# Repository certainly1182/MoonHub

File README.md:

# MoonHub - Unified Daughterboard-esque USB 2.0 Hub
This repository contains the hardware for a USB hub designed for mechanical keyboards.
Designed for use with the [MoonBoard](https://github.com/certainly1182/MoonBoard).

## Features
- USB-C input, 1x USB-C output, 2x USB-A output, 1x Molex EZMate.
- USB 2.0 high-speed with MTT for downstream ports.
- Overcurrent limit.
- ESD Protection.

## Images

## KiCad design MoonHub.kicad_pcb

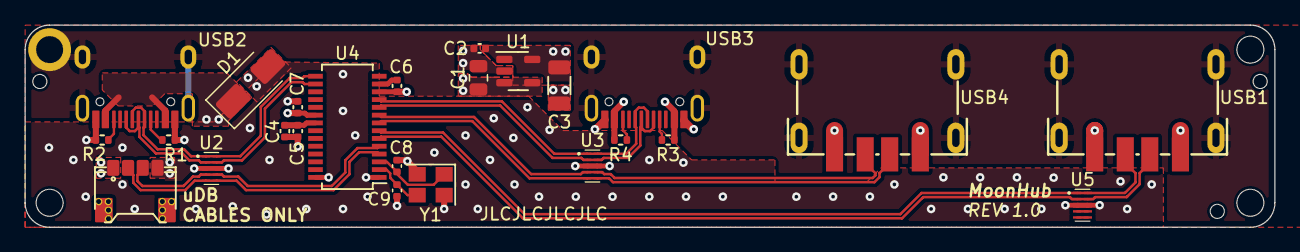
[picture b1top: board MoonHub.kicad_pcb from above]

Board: 4 copper layers, 102.0 x 16.5 mm, 32 parts (0 on the bottom side), 22 nets.

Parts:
C1: 10u; C_0805_2012Metric
C2, C5: 100n; C_0402_1005Metric
C3: 100u; C_1206_3216Metric
C4: 10u; C_0402_1005Metric
C6, C7: 1u; C_0402_1005Metric
C8, C9: 20p; C_0402_1005Metric
D1: SMAJ5.0A; D_SMA
H1, H3, H4: MountingHole; MountingHole_2.2mm_M2_ISO7380
H2: MountingHole_Pad; Generic-Mounthole-Plated
H5, H6, H7: ToolingHole; JLC-Tooling-Hole
J1: X1224WRS-04-LPV01; UDB-PicoEZMate-Reinforced-Alt
R1, R2: 5k1; R_0402_1005Metric
R3, R4: 56k; R_0402_1005Metric
U1: AP22818AKBWT-7; SOT-23-5
U2, U3, U5: H5VU25U; DFN2510
U4: CH334U; SSOP-28_3.9x9.9mm_P0.635mm
USB1, USB4: USB_A; USB-A-SMD_USB-M-21_914-441A2021S10200
USB2, USB3: USB_C_Receptacle_USB2.0; HRO-TYPE-C-31-M-12-Assembly
Y1: 12MHz; Crystal_SMD_3225-4Pin_3.2x2.5mm

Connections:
+5V: C1.1, C7.1, D1.1 (A1), U1.3 (IN), U1.4 (EN), U4.20 (V5), USB2.A4 (VBUS), USB2.B4 (VBUS)
/USB1_D+: U3.1 (IO1), U3.10 (NC), U4.11 (DP1), USB3.A6 (D+), USB3.B6 (D+)
/USB1_D-: U3.2 (IO2), U3.9 (NC), U4.10 (DM1), USB3.A7 (D-), USB3.B7 (D-)
/USB2_D+: U3.4 (D2+), U3.7 (NC), U4.9 (DP2), USB4.3 (D+)
/USB2_D-: U3.5 (D2-), U3.6 (NC), U4.8 (DM2), USB4.2 (D-)
/USB3_D+: U4.7 (DP3), U5.1 (IO1), U5.10 (NC), USB1.3 (D+)
/USB3_D-: U4.6 (DM3), U5.2 (IO2), U5.9 (NC), USB1.2 (D-)
/USB4_D+: J1.3, U2.4 (D2+), U2.7 (NC), U4.5 (DP4)
/USB4_D-: J1.2, U2.5 (D2-), U2.6 (NC), U4.4 (DM4)
/USBU_D+: U2.2 (IO2), U2.9 (NC), U4.16 (DPU), USB2.A6 (D+), USB2.B6 (D+)
/USBU_D-: U2.1 (IO1), U2.10 (NC), U4.15 (DMU), USB2.A7 (D-), USB2.B7 (D-)
GND: C1.2, C2.2, C3.2, C4.2, C5.2, C6.2, C7.2, C8.2, C9.2, D1.2 (A2), J1.4, R1.2, R2.2, U1.2 (GND), U2.3 (GND), U2.8 (GND), U3.3 (GND), U3.8 (GND), U4.1 (GND), U4.12 (GND), U4.28 (GND), U5.3 (GND), U5.8 (GND), USB1.4 (GND), USB2.A1 (GND), USB2.B1 (GND), USB3.A1 (GND), USB3.B1 (GND), USB4.4 (GND), Y1.2, Y1.4
GNDPWR: H2.1, J1.MP (MountPin), USB1.5 (Shield), USB2.S1 (SHIELD), USB3.S1 (SHIELD), USB4.5 (Shield)
unnamed: C4.1, C5.1, U4.21 (VDD33)
unnamed: C6.1, U4.13 (VDD33)
unnamed: C8.1, U4.3 (XI), Y1.1
unnamed: C9.1, U4.2 (XO), Y1.3
unnamed: R1.1, USB2.A5 (CC1)
unnamed: R2.1, USB2.B5 (CC2)
unnamed: R3.2, USB3.A5 (CC1)
unnamed: R4.2, USB3.B5 (CC2)
VBUS: C2.1, C3.1, J1.1, R3.1, R4.1, U1.1 (OUT), U1.5 (OUT), USB1.1 (VBUS), USB3.A4 (VBUS), USB3.B4 (VBUS), USB4.1 (VBUS)

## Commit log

2023-09-04 second commmit
2023-09-04 add license
2023-09-04 remove unused schematic
2023-09-05 fully routed
2023-09-07 reroute for smaller size
2023-09-19 move uDB connector & switch current limit
2023-09-26 redo esd protection
2023-10-10 export step
2023-10-18 change usb esd array
2024-01-21 remove ferrites
2024-02-18 change ESD
2024-05-08 update to KiCad 8
2024-05-08 repo name error
